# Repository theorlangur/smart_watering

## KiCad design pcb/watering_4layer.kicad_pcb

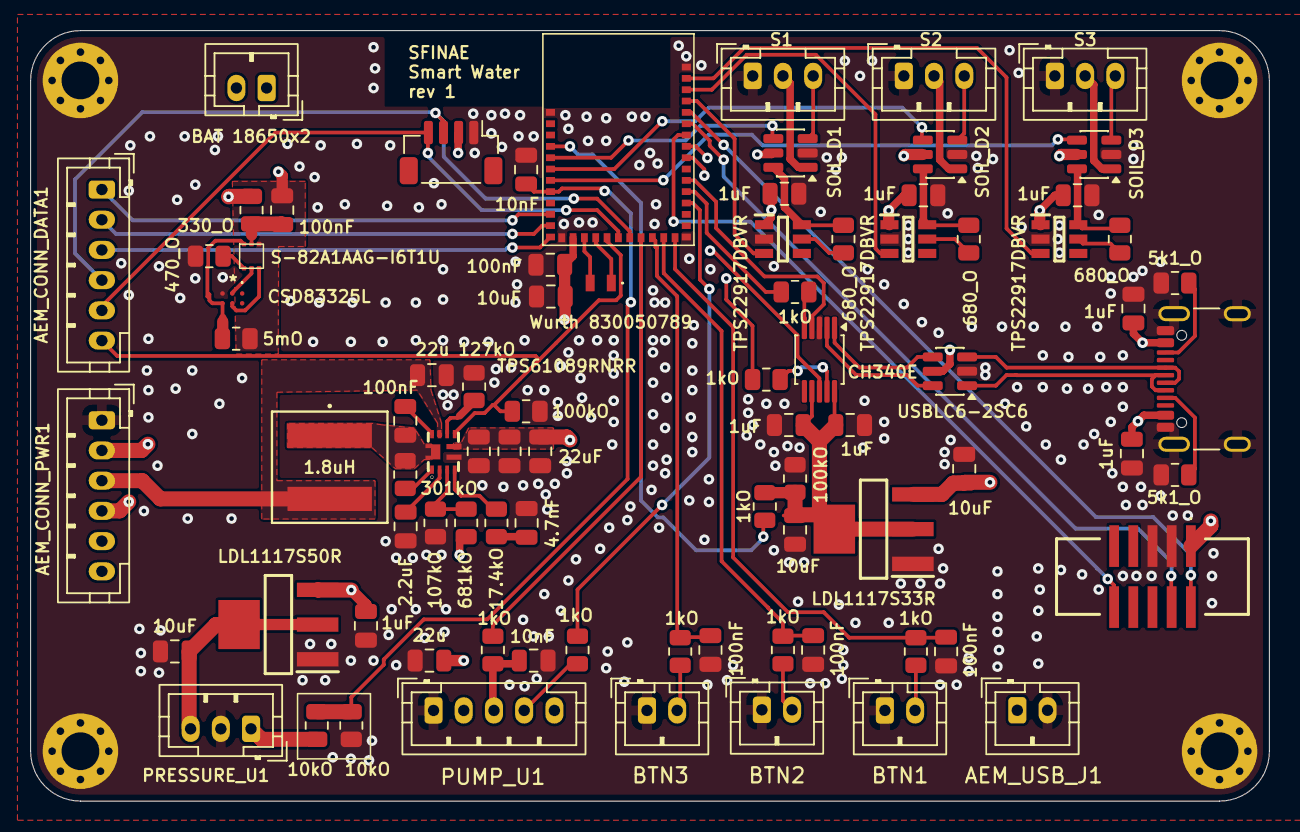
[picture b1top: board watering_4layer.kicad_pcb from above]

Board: 4 copper layers, 82.0 x 51.0 mm, 87 parts (0 on the bottom side), 76 nets.

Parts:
AEM_CONN_DATA1: Conn_01x06; JST_PH_B6B-PH-K_1x06_P2.00mm_Vertical
AEM_CONN_PWR1: Conn_01x06; JST_PH_B6B-PH-K_1x06_P2.00mm_Vertical
AEM_USB_J1: Conn_01x02; JST_PH_B2B-PH-K_1x02_P2.00mm_Vertical
BAT_C1: 100nF; C_0805_2012Metric
BAT_IC1: S-82A1AAG-I6T1U; S-82A1A
BAT_J1: BAT 18650x2; JST_PH_B2B-PH-K_1x02_P2.00mm_Vertical
BAT_Q1: CSD83325L
BAT_R1: 330_O; R_0805_2012Metric
BAT_R2: 470_O; R_0805_2012Metric
BAT_R3: 5mO; R_0805_2012Metric
BOOST_9V_C1, BOOST_9V_C2: 22u; C_0805_2012Metric
BOOST_9V_C3: 2.2uF; C_0805_2012Metric
BOOST_9V_C4: 100nF; C_0805_2012Metric
BOOST_9V_C5: 4.7nF; C_0805_2012Metric
BOOST_9V_C6, BOOST_9V_C7, BOOST_9V_C8: 22uF; C_0805_2012Metric
BOOST_9V_L1: 1.8uH; IND_EXLA1V0606_EAT
BOOST_9V_R1: 681kO; R_0805_2012Metric
BOOST_9V_R2: 107kO; R_0805_2012Metric
BOOST_9V_R3: 301kO; R_0805_2012Metric
BOOST_9V_R4: 127kO; R_0805_2012Metric
BOOST_9V_R5: 17.4kO; R_0805_2012Metric
BOOST_IC1: TPS61089RNRR; TPS61089
BTN1: Boot; JST_PH_B2B-PH-K_1x02_P2.00mm_Vertical
BTN2: ZB; JST_PH_B2B-PH-K_1x02_P2.00mm_Vertical
BTN3: CTRL; JST_PH_B2B-PH-K_1x02_P2.00mm_Vertical
BTN_C1, BTN_C2, BTN_C3: 100nF; C_0805_2012Metric
BTN_R1, BTN_R2, BTN_R3: 1kO; R_0805_2012Metric
H1, H2, H3, H4: MountingHole; MountingHole_2.5mm_Pad_Via
IC1: LDL1117S33R
MCU_C1: 10uF; C_0805_2012Metric
MCU_C2: 100nF; C_0805_2012Metric
MCU_IC1: ezurio_bl54l15_453-00001R; Laird, BL54L15 Module, Platform Side
MCU_Y1: Wurth 830050789; Wurth-XTAL-830050789
PRESSURE_C1: 10uF; C_0805_2012Metric
PRESSURE_C2: 1uF; C_0805_2012Metric
PRESSURE_C3: 10nF; C_0805_2012Metric
PRESSURE_IC1: LDL1117S50R
PRESSURE_R1, PRESSURE_R2: 10kO; R_0805_2012Metric
PRESSURE_U1: JST_PH_B3B-PH-K_1x03_P2.00mm_Vertical
PUMP_C1: 10nF; C_0805_2012Metric
PUMP_R1: 100kO; R_0805_2012Metric
PUMP_R2, PUMP_R3: 1kO; R_0805_2012Metric
PUMP_U1: JST_PH_B5B-PH-K_1x05_P2.00mm_Vertical
SENSE_C1, SENSE_C2, SENSE_C3: 1uF; C_0805_2012Metric
SENSE_LOAD1, SENSE_LOAD2, SENSE_LOAD3: TPS22917DBVR
SENSE_LOAD_QOD1, SENSE_LOAD_QOD2, SENSE_LOAD_QOD3: 680_O; R_0805_2012Metric
SENSE_S1: JST_SH_BM04B-SRSS-TB_1x04-1MP_P1.00mm_Vertical
SENSE_U2: S1; JST_PH_B3B-PH-K_1x03_P2.00mm_Vertical
SENSE_U3: S2; JST_PH_B3B-PH-K_1x03_P2.00mm_Vertical
SENSE_U4: S3; JST_PH_B3B-PH-K_1x03_P2.00mm_Vertical
SOIL_D1, SOIL_D2, SOIL_D3: USBLC6-2SC6; SOT-23-6
SWD_J1: IDC Box Header; IDC Box Header 2x5 1.27
UART_C1, UART_C2: 1uF; C_0805_2012Metric
UART_R1, UART_R2: 1kO; R_0805_2012Metric
UART_U1: CH340E; MSOP-10_3x3mm_P0.5mm
USB_C1, USB_C2: 10uF; C_0805_2012Metric
USB_C3, USB_C4: 1uF; C_0805_2012Metric
USB_D1: USBLC6-2SC6; SOT-23-6
USB_J1: USB_C_Receptacle_USB2.0_16P; USB_C_Receptacle_GCT_USB4105-xx-A_16P_TopMnt_Horizontal
USB_R1, USB_R2: 5k1_O; R_0805_2012Metric
USB_R3: 100kO; R_0805_2012Metric
USB_R4: 1kO; R_0805_2012Metric

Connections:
+3V3: AEM_CONN_PWR1.2, MCU_C1.1, MCU_C2.1, MCU_IC1.26 (VDD_NRF), SENSE_C1.2, SENSE_C2.2, SENSE_C3.2, SENSE_LOAD1.1 (VIN), SENSE_LOAD2.1 (VIN), SENSE_LOAD3.1 (VIN), SENSE_S1.2 (VCC), SOIL_D1.5 (VBUS), SOIL_D2.5 (VBUS), SOIL_D3.5 (VBUS), SWD_J1.1
+4V2: AEM_CONN_PWR1.3, BOOST_9V_C1.1, BOOST_9V_L1.2, BOOST_IC1.9 (VIN)
+5V: PRESSURE_C1.1, PRESSURE_IC1.2 (VOUT_1), PRESSURE_IC1.4 (VOUT_2), PRESSURE_U1.3 (VCC)
+9V: BOOST_9V_C2.1, BOOST_9V_C6.1, BOOST_9V_C7.1, BOOST_9V_C8.1, BOOST_9V_R1.1, BOOST_IC1.6 (VOUT), PRESSURE_C2.1, PRESSURE_IC1.3 (VIN), PUMP_U1.2 (VCC)
+VBUS: AEM_USB_J1.1, IC1.3 (VIN), USB_C1.2, USB_C3.2, USB_C4.2, USB_D1.5 (VBUS), USB_J1.A4 (VBUS), USB_J1.A9 (VBUS), USB_J1.B4 (VBUS), USB_J1.B9 (VBUS)
/AEM_IRQ: AEM_CONN_DATA1.3, MCU_IC1.28 (P1.10)
/AEM_LOAD: AEM_CONN_DATA1.1, MCU_IC1.30 (P1.08/EXTREF/CLK16M/_CLK)
/AEM_PWR_STO: AEM_CONN_PWR1.4, BAT_J1.2, BAT_R1.1
/AEM_STO: AEM_CONN_DATA1.2, MCU_IC1.29 (P1.09)
/BOOST_9V_SW: BOOST_9V_C4.1, BOOST_9V_L1.1, BOOST_9V_R3.1, BOOST_IC1.11 (SW)
/BTN_BOOT: BTN_C1.1, BTN_R1.2, MCU_IC1.17 (P0.00_)
/BTN_CTRL: BTN_C3.1, BTN_R3.2, MCU_IC1.19 (P0.02)
/BTN_ZB: BTN_C2.1, BTN_R2.2, MCU_IC1.18 (P0.01_)
/I2C_SDA: AEM_CONN_DATA1.4, MCU_IC1.21 (P1.06/AIN2), SENSE_S1.3 (SDA)
/I2C_SDC: AEM_CONN_DATA1.5, MCU_IC1.22 (P1.05/AIN1_), SENSE_S1.4 (SDC)
/PRESSURE_OUT: PRESSURE_R1.2, PRESSURE_U1.1 (OUT)
/PUMP_OUT: PUMP_C1.1, PUMP_R2.1, PUMP_U1.3 (OUT)
/PUMP_POWER_CTRL: AEM_CONN_DATA1.6, BOOST_IC1.7 (EN), MCU_IC1.23 (P1.04/AIN0/CLK), PUMP_R1.2
/PUMP_PWM: PUMP_R3.1, PUMP_U1.4 (PWM)
/SOIL1_OUT: MCU_IC1.35 (P1.11/AIN4/CLK), SOIL_D1.4 (I/O2)
/SOIL1_VCC: MCU_IC1.4 (P2.07), SENSE_LOAD1.3 (ON)
/SOIL2_OUT: MCU_IC1.34 (P1.12/AIN5/CLK), SOIL_D2.4 (I/O2)
/SOIL2_VCC: MCU_IC1.3 (P2.08), SENSE_LOAD2.3 (ON)
/SOIL3_OUT: MCU_IC1.33 (P1.13/AIN6), SOIL_D3.4 (I/O2)
/SOIL3_VCC: MCU_IC1.2 (P2.09), SENSE_LOAD3.3 (ON)
/SWDCLK: MCU_IC1.6 (SWDCLK), SWD_J1.4
/SWDIO: MCU_IC1.5 (SWDIO), SWD_J1.2
/UART00_CTS: MCU_IC1.11 (P2.04), UART_U1.4 (~RTS)
/UART00_RTS: UART_R2.2, UART_U1.5 (~CTS)
/UART00_RX: MCU_IC1.9 (P2.00), UART_U1.8 (TXD)
/UART00_TX: UART_R1.2, UART_U1.9 (RXD)
/USBCD+: USB_D1.3 (I/O2), USB_J1.A6 (D+), USB_J1.B6 (D+)
/USBCD-: USB_D1.1 (I/O1), USB_J1.A7 (D-), USB_J1.B7 (D-)
/USBD+: UART_U1.1 (UD+), USB_D1.4 (I/O2)
/USBD-: UART_U1.2 (UD-), USB_D1.6 (I/O1)
/XL1: MCU_IC1.25 (P1.00/XL1_), MCU_Y1.2
/XL2: MCU_IC1.24 (P1.01/XL2_), MCU_Y1.1
/nRST: MCU_IC1.7 (NRESET), SWD_J1.10
BATT_GND: BAT_C1.2, BAT_IC1.4 (VSS), BAT_J1.1, BAT_R3.1
GND: AEM_CONN_PWR1.1, AEM_USB_J1.2, BAT_Q1.C1 (S1_2), BAT_R2.2, BOOST_9V_C1.2, BOOST_9V_C2.2, BOOST_9V_C3.2, BOOST_9V_C5.2, BOOST_9V_C6.2, BOOST_9V_C7.2, BOOST_9V_C8.2, BOOST_9V_R2.2, BOOST_9V_R4.2, BOOST_IC1.5 (GND), BTN1.1, BTN2.1, BTN3.1, BTN_C1.2, BTN_C2.2, BTN_C3.2, H1.1 (1_1), H2.1 (1_1), H3.1 (1_1), H4.1 (1_1), IC1.1 (GND), MCU_C1.2, MCU_C2.2, MCU_IC1.1 (GND_1), MCU_IC1.16 (GND_2), MCU_IC1.27 (GND_3), MCU_IC1.39 (GND_4), PRESSURE_C1.2, PRESSURE_C2.2, PRESSURE_C3.2, PRESSURE_IC1.1 (GND), PRESSURE_R2.1, PRESSURE_U1.2 (GND), PUMP_C1.2, PUMP_R1.1, PUMP_U1.1 (GND), SENSE_C1.1, SENSE_C2.1, SENSE_C3.1, SENSE_LOAD1.2 (GND), SENSE_LOAD2.2 (GND), SENSE_LOAD3.2 (GND), SENSE_S1.1 (GND), SENSE_U2.1 (GND), SENSE_U3.1 (GND), SENSE_U4.1 (GND), SOIL_D1.2 (GND), SOIL_D2.2 (GND), SOIL_D3.2 (GND), SWD_J1.3, SWD_J1.5, UART_C1.2, UART_C2.2, UART_U1.3 (GND), USB_C1.1, USB_C2.2, USB_C3.1, USB_C4.1, USB_D1.2 (GND), USB_J1.A1 (GND), USB_J1.A12 (GND), USB_J1.B1 (GND), USB_J1.B12 (GND), USB_J1.SH (SHIELD), USB_R1.2, USB_R2.2, USB_R3.2
unnamed: BAT_IC1.2 (CO), BAT_Q1.B1 (G1)
unnamed: BAT_IC1.3 (DO), BAT_Q1.B2 (G2)
unnamed: BAT_C1.1, BAT_IC1.5 (VDD), BAT_R1.2
unnamed: BAT_IC1.6 (VINI), BAT_Q1.C2 (S2_2), BAT_R3.2
unnamed: BAT_IC1.1 (VM), BAT_R2.1
unnamed: BOOST_9V_C5.1, BOOST_9V_R5.1
unnamed: BOOST_9V_C4.2, BOOST_IC1.10 (BOOT)
unnamed: BOOST_9V_R5.2, BOOST_IC1.4 (COMP)
unnamed: BOOST_9V_R1.2, BOOST_9V_R2.1, BOOST_IC1.3 (FB)
unnamed: BOOST_9V_R3.2, BOOST_IC1.1 (FSW)
unnamed: BOOST_9V_R4.1, BOOST_IC1.8 (ILIM)
unnamed: BOOST_9V_C3.1, BOOST_IC1.2 (VCC)
unnamed: BTN1.2, BTN_R1.1
unnamed: BTN2.2, BTN_R2.1
unnamed: BTN3.2, BTN_R3.1
unnamed: MCU_IC1.36 (P0.03/CLK), USB_R4.1
unnamed: MCU_IC1.20 (P1.07/AIN3), PUMP_R2.2
unnamed: MCU_IC1.32 (P1.14/AIN7), PRESSURE_C3.1, PRESSURE_R1.1, PRESSURE_R2.2
unnamed: MCU_IC1.8 (P2.02_), UART_R1.1
unnamed: MCU_IC1.13 (P2.03), PUMP_R3.2
unnamed: MCU_IC1.12 (P2.05), UART_R2.1
unnamed: SENSE_LOAD1.5 (QOD), SENSE_LOAD_QOD1.1
unnamed: SENSE_LOAD1.6 (VOUT), SENSE_LOAD_QOD1.2, SOIL_D1.6 (I/O1)
unnamed: SENSE_LOAD2.5 (QOD), SENSE_LOAD_QOD2.1
unnamed: SENSE_LOAD2.6 (VOUT), SENSE_LOAD_QOD2.2, SOIL_D2.6 (I/O1)
unnamed: SENSE_LOAD3.5 (QOD), SENSE_LOAD_QOD3.1
unnamed: SENSE_LOAD3.6 (VOUT), SENSE_LOAD_QOD3.2, SOIL_D3.6 (I/O1)
unnamed: SENSE_U2.3 (OUT), SOIL_D1.3 (I/O2)
unnamed: SENSE_U2.2 (VCC), SOIL_D1.1 (I/O1)
unnamed: SENSE_U3.3 (OUT), SOIL_D2.3 (I/O2)
unnamed: SENSE_U3.2 (VCC), SOIL_D2.1 (I/O1)
unnamed: SENSE_U4.3 (OUT), SOIL_D3.3 (I/O2)
unnamed: SENSE_U4.2 (VCC), SOIL_D3.1 (I/O1)
unnamed: USB_J1.A5 (CC1), USB_R2.1
unnamed: USB_J1.B5 (CC2), USB_R1.1
USB_3.3V: IC1.2 (VOUT_1), IC1.4 (VOUT_2), UART_C1.1, UART_C2.1, UART_U1.7 (VCC), UART_U1.10 (V3), USB_C2.1, USB_R3.1, USB_R4.2

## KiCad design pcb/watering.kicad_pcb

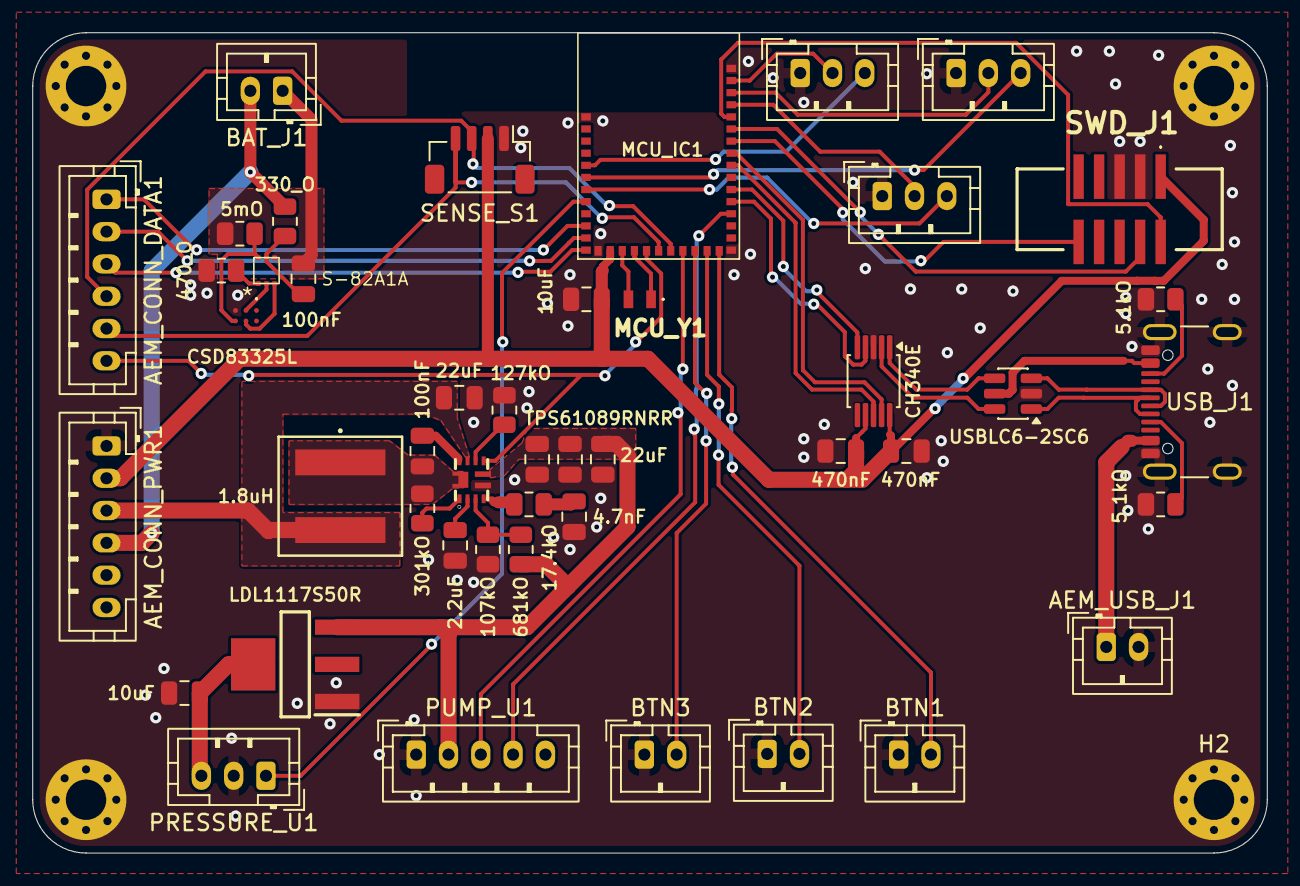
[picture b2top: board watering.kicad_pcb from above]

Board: 2 copper layers, 76.5 x 50.8 mm, 50 parts (0 on the bottom side), 54 nets.

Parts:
1.8uH: 1.8uH; IND_EXLA1V0606_EAT
2.2uF: 2.2u; C_0805_2012Metric
4.7nF: 4.7n; C_0805_2012Metric
5.1kO, 5.1kO#2: 5k1; R_0805_2012Metric
5mO: 5mO; R_0805_2012Metric
10uF, 10uF#2: 10u; C_0805_2012Metric
17.4kO: 17.4k; R_0805_2012Metric
22uF, 22uF#2: 22u; C_0805_2012Metric
100nF, 100nF#2: 100n; C_0805_2012Metric
107kO: 107k; R_0805_2012Metric
127kO: 127k; R_0805_2012Metric
301kO: 301k; R_0805_2012Metric
330_O: 330; R_0805_2012Metric
470_O: 470; R_0805_2012Metric
470nF, 470nF#2: 470n; C_0805_2012Metric
681kO: 681k; R_0805_2012Metric
AEM_CONN_DATA1: Conn_01x06; JST_PH_B6B-PH-K_1x06_P2.00mm_Vertical
AEM_CONN_PWR1: Conn_01x06; JST_PH_B6B-PH-K_1x06_P2.00mm_Vertical
AEM_USB_J1: Conn_01x02; JST_PH_B2B-PH-K_1x02_P2.00mm_Vertical
BAT_J1: BAT 18650x2; JST_PH_B2B-PH-K_1x02_P2.00mm_Vertical
BOOST_9V_C6, BOOST_9V_C7: 22u; C_0805_2012Metric
BTN1: Boot; JST_PH_B2B-PH-K_1x02_P2.00mm_Vertical
BTN2: ZB; JST_PH_B2B-PH-K_1x02_P2.00mm_Vertical
BTN3: CTRL; JST_PH_B2B-PH-K_1x02_P2.00mm_Vertical
CH340E: CH340E; MSOP-10_3x3mm_P0.5mm
CSD83325L: CSD83325L
H1, H2, H3, H4: MountingHole; MountingHole_2.5mm_Pad_Via
LDL1117S50R: LDL1117S50R
MCU_IC1: ezurio_bl54l15_453-00001R; Laird, BL54L15 Module, Platform Side
MCU_Y1: Wurth 830050789; Wurth-XTAL-830050789
PRESSURE_U1: JST_PH_B3B-PH-K_1x03_P2.00mm_Vertical
PUMP_U1: JST_PH_B5B-PH-K_1x05_P2.00mm_Vertical
S-82A1A: S-82A1AAG-I6T1U; S-82A1A
SENSE_S1: JST_SH_BM04B-SRSS-TB_1x04-1MP_P1.00mm_Vertical
SENSE_U2, SENSE_U3, SENSE_U4: JST_PH_B3B-PH-K_1x03_P2.00mm_Vertical
SWD_J1: IDC Box Header; IDC Box Header 2x5 1.27
TPS61089RNRR: TPS61089RNRR; TPS61089
USBLC6-2SC6: USBLC6-2SC6; SOT-23-6
USB_J1: USB_C_Receptacle_USB2.0_16P; USB_C_Receptacle_GCT_USB4105-xx-A_16P_TopMnt_Horizontal

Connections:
+3V3: 10uF.1, 470nF.1, 470nF#2.1, AEM_CONN_PWR1.2, CH340E.7 (VCC), CH340E.10 (V3), MCU_IC1.26 (VDD_NRF), SENSE_S1.2 (VCC), SWD_J1.1
+4V2: 1.8uH.2, 22uF#2.1, AEM_CONN_PWR1.3, TPS61089RNRR.9 (VIN)
+5V: 10uF#2.1, LDL1117S50R.4 (VOUT_2), PRESSURE_U1.3 (VCC)
+9V: 22uF.1, 681kO.1, BOOST_9V_C6.1, BOOST_9V_C7.1, LDL1117S50R.3 (VIN), PUMP_U1.2 (VCC), TPS61089RNRR.6 (VOUT)
+VBUS: AEM_USB_J1.1, USBLC6-2SC6.5 (VBUS), USB_J1.A4 (VBUS), USB_J1.A9 (VBUS), USB_J1.B4 (VBUS), USB_J1.B9 (VBUS)
/AEM_IRQ: AEM_CONN_DATA1.3, MCU_IC1.28 (P1.10)
/AEM_LOAD: AEM_CONN_DATA1.1, MCU_IC1.30 (P1.08/EXTREF/CLK16M/_CLK)
/AEM_PWR_STO: 330_O.1, AEM_CONN_PWR1.4, BAT_J1.2
/AEM_STO: AEM_CONN_DATA1.2, MCU_IC1.29 (P1.09)
/BOOST_9V_SW: 1.8uH.1, 100nF.1, 301kO.1, TPS61089RNRR.11 (SW)
/BTN_BOOT: BTN1.2, MCU_IC1.17 (P0.00_)
/BTN_CTRL: BTN3.2, MCU_IC1.19 (P0.02)
/BTN_ZB: BTN2.2, MCU_IC1.18 (P0.01_)
/I2C_SDA: AEM_CONN_DATA1.4, MCU_IC1.21 (P1.06/AIN2), SENSE_S1.3 (SDA)
/I2C_SDC: AEM_CONN_DATA1.5, MCU_IC1.22 (P1.05/AIN1_), SENSE_S1.4 (SDC)
/PRESSURE_OUT: MCU_IC1.32 (P1.14/AIN7), PRESSURE_U1.1 (OUT)
/PUMP_OUT: MCU_IC1.20 (P1.07/AIN3), PUMP_U1.3 (OUT)
/PUMP_POWER_CTRL: AEM_CONN_DATA1.6, MCU_IC1.23 (P1.04/AIN0/CLK), TPS61089RNRR.7 (EN)
/PUMP_PWM: MCU_IC1.13 (P2.03), PUMP_U1.4 (PWM)
/SOIL1_OUT: MCU_IC1.35 (P1.11/AIN4/CLK), SENSE_U2.3 (OUT)
/SOIL1_VCC: MCU_IC1.2 (P2.09), SENSE_U2.2 (VCC)
/SOIL2_OUT: MCU_IC1.34 (P1.12/AIN5/CLK), SENSE_U3.3 (OUT)
/SOIL2_VCC: MCU_IC1.3 (P2.08), SENSE_U3.2 (VCC)
/SOIL3_OUT: MCU_IC1.33 (P1.13/AIN6), SENSE_U4.3 (OUT)
/SOIL3_VCC: MCU_IC1.4 (P2.07), SENSE_U4.2 (VCC)
/SWDCLK: MCU_IC1.6 (SWDCLK), SWD_J1.4
/SWDIO: MCU_IC1.5 (SWDIO), SWD_J1.2
/UART00_CTS: CH340E.5 (~CTS), MCU_IC1.11 (P2.04)
/UART00_RTS: CH340E.4 (~RTS), MCU_IC1.12 (P2.05)
/UART00_RX: CH340E.8 (TXD), MCU_IC1.9 (P2.00)
/UART00_TX: CH340E.9 (RXD), MCU_IC1.8 (P2.02_)
/USBCD+: USBLC6-2SC6.3 (I/O2), USB_J1.A6 (D+), USB_J1.B6 (D+)
/USBCD-: USBLC6-2SC6.1 (I/O1), USB_J1.A7 (D-), USB_J1.B7 (D-)
/USBD+: CH340E.1 (UD+), USBLC6-2SC6.4 (I/O2)
/USBD-: CH340E.2 (UD-), USBLC6-2SC6.6 (I/O1)
/XL1: MCU_IC1.25 (P1.00/XL1_), MCU_Y1.2
/XL2: MCU_IC1.24 (P1.01/XL2_), MCU_Y1.1
/nRST: MCU_IC1.7 (NRESET), SWD_J1.10
BATT_GND: 5mO.1, 100nF#2.2, BAT_J1.1, S-82A1A.4 (VSS)
GND: 2.2uF.2, 4.7nF.2, 5.1kO.2, 5.1kO#2.2, 10uF.2, 10uF#2.2, 22uF.2, 22uF#2.2, 107kO.2, 127kO.2, 470_O.2, 470nF.2, 470nF#2.2, AEM_CONN_PWR1.1, AEM_USB_J1.2, BOOST_9V_C6.2, BOOST_9V_C7.2, BTN1.1, BTN2.1, BTN3.1, CH340E.3 (GND), CSD83325L.C1 (S1_2), H1.1 (1_1), H2.1 (1_1), H3.1 (1_1), H4.1 (1_1), LDL1117S50R.1 (GND), MCU_IC1.1 (GND_1), MCU_IC1.16 (GND_2), MCU_IC1.27 (GND_3), MCU_IC1.39 (GND_4), PRESSURE_U1.2 (GND), PUMP_U1.1 (GND), SENSE_S1.1 (GND), SENSE_U2.1 (GND), SENSE_U3.1 (GND), SENSE_U4.1 (GND), SWD_J1.3, SWD_J1.5, TPS61089RNRR.5 (GND), USBLC6-2SC6.2 (GND), USB_J1.A1 (GND), USB_J1.A12 (GND), USB_J1.B1 (GND), USB_J1.B12 (GND), USB_J1.SH (SHIELD)
unnamed: CSD83325L.B1 (G1), S-82A1A.2 (CO)
unnamed: CSD83325L.B2 (G2), S-82A1A.3 (DO)
unnamed: 100nF#2.1, 330_O.2, S-82A1A.5 (VDD)
unnamed: 5mO.2, CSD83325L.C2 (S2_2), S-82A1A.6 (VINI)
unnamed: 470_O.1, S-82A1A.1 (VM)
unnamed: 4.7nF.1, 17.4kO.1
unnamed: 100nF.2, TPS61089RNRR.10 (BOOT)
unnamed: 17.4kO.2, TPS61089RNRR.4 (COMP)
unnamed: 107kO.1, 681kO.2, TPS61089RNRR.3 (FB)
unnamed: 301kO.2, TPS61089RNRR.1 (FSW)
unnamed: 127kO.1, TPS61089RNRR.8 (ILIM)
unnamed: 2.2uF.1, TPS61089RNRR.2 (VCC)
unnamed: 5.1kO.1, USB_J1.A5 (CC1)
unnamed: 5.1kO#2.1, USB_J1.B5 (CC2)
